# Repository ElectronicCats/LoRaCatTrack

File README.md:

# LoRaCat: Track

Electronic Cats invests time and resources providing this open source design, please support Electronic Cats and open-source hardware by purchasing products from Electronic Cats!

Designed by Electronic Cats.

Firmware released under an GNU AGPL v3.0 license. See the LICENSE file for more information.

Hardware released under an CERN Open Hardware Licence v1.2. See the LICENSE_HARDWARE file for more information.

Electronic Cats is a registered trademark, please do not use if you sell these PCBs.

23 Nov 2016

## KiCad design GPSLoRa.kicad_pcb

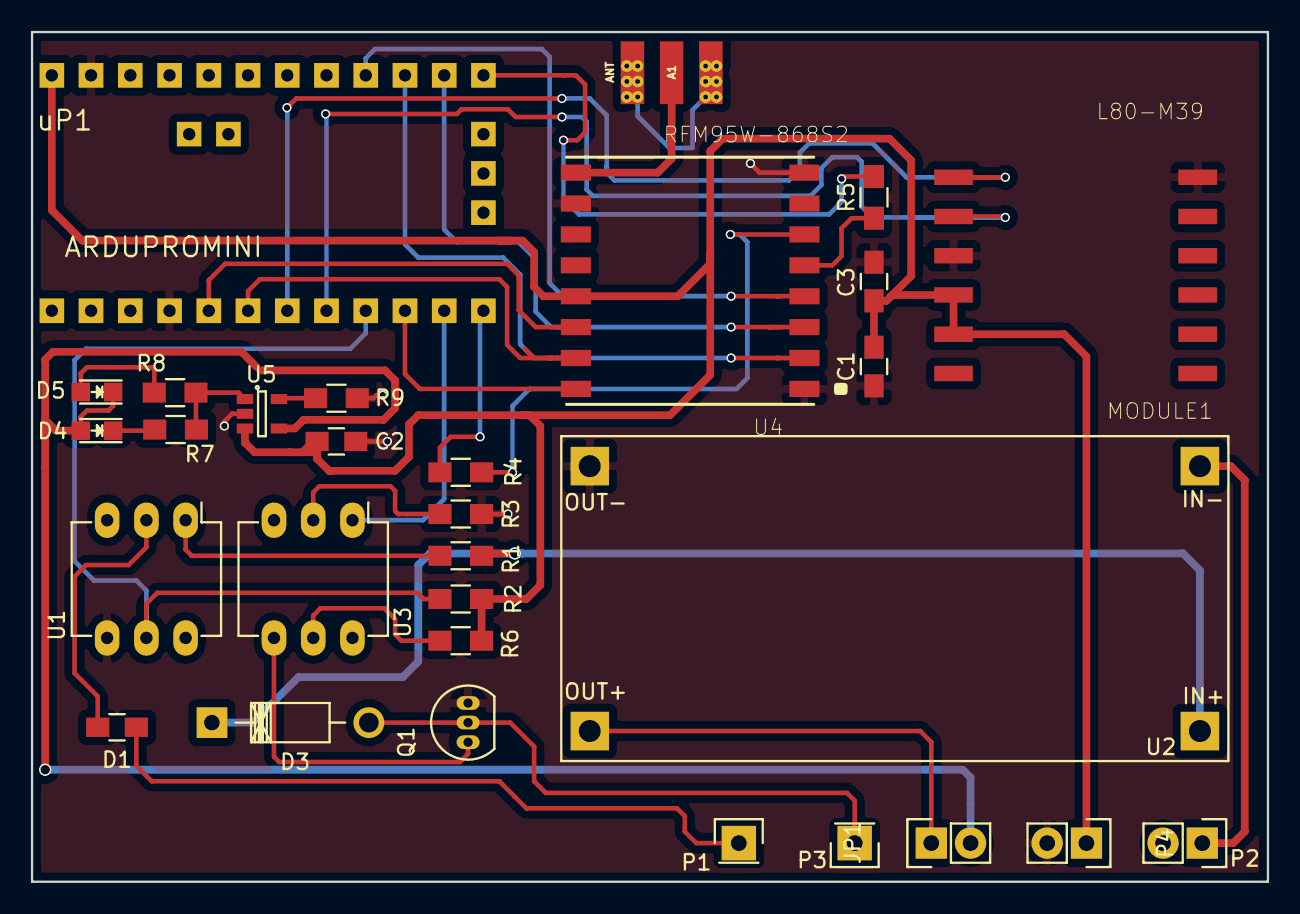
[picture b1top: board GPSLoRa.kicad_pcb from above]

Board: 2 copper layers, 80.0 x 55.0 mm, 30 parts (0 on the bottom side), 32 nets.

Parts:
A1: ANT; GSG-SMA-EDGE
C1, C3: 0.1uF; C_0805_HandSoldering
C2: 10uF; C_0805_HandSoldering
D1: D; C_0805_HandSoldering
D3: D; Diode_DO-41_SOD81_Horizontal_RM10
D4, D5: LED; LED_0805
JP1: JUMPER; Pin_Header_Straight_1x02
MODULE1: L80-M39; QUECTEL_L80-M39
P1: IN EXT; Pin_Header_Straight_1x01
P2: - INPUT 12 +; Pin_Header_Straight_1x02
P3: OUT EXT; Pin_Header_Straight_1x01
P4: Battery; Pin_Header_Straight_1x02
Q1: Q_NPN_BCE; TO-92_Inline_Narrow_Oval
R1, R6, R9: 1K; R_0805_HandSoldering
R2, R4, R5: 10K; R_0805_HandSoldering
R3, R7, R8: 220R; R_0805_HandSoldering
U1, U3: 4N26; DIP-6_W7.62mm_LongPads
U2: LM2596_Breakout; LM2596DC-DC
U4: RFM95W-868S2; XCVR_RFM95W-868S2
U5: MCP73831T-2ATI/OT; SOT-23-5
uP1: ARDUPROMINI; arduinoMiniPro2

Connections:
+5V: D4.2, D5.1, JP1.2, U5.4
+12C: D3.1, R1.1, U2.1
+BATT: C1.1, C2.1, C3.1, MODULE1.4, MODULE1.5, P4.1, R2.1, R6.1, U4.13, U5.3, uP1.19
/D6: R2.2, U1.5, uP1.15
/D8: U3.1, uP1.17
/DIO0: U4.14, uP1.11
/DIO1: U4.15, uP1.12
/DIO2: U4.16, uP1.16
/MISO: U4.2, uP1.28
/MOSI: U4.3, uP1.29
/NSS: R5.1, uP1.30
/RST: R4.1, uP1.18
/RX: MODULE1.2, uP1.14
/SCK: U4.4, uP1.27
/TX: MODULE1.1, uP1.13
GND: A1.2, A1.3, A1.4, A1.5, C1.2, C2.2, C3.2, MODULE1.3, MODULE1.12, P4.2, Q1.3, R3.2, R9.2, U1.4, U2.4, U4.1, U4.8, U4.10, U5.2, uP1.10, uP1.20
unnamed: A1.1, U4.9
unnamed: D1.1, P1.1
unnamed: D1.2, U1.2
unnamed: D3.2, P3.1, Q1.2
unnamed: D4.1, R7.2
unnamed: D5.2, R8.2
unnamed: JP1.1, U2.3
unnamed: P2.1, U2.2
unnamed: Q1.1, U3.4
unnamed: R1.2, U1.1
unnamed: R3.1, U3.2
unnamed: R4.2, U4.6
unnamed: R5.2, U4.5
unnamed: R6.2, U3.5
unnamed: R7.1, R8.1, U5.1
unnamed: R9.1, U5.5

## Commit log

2016-11-21 Added Squematic
2016-11-23 Working LoRa OTAA
2016-11-24 ChangeName LoRaCatTrack
2016-11-24 Added PDF v0.2
2016-11-25 Added PCB
2016-11-30 Modificado pines NSS y RST
2016-12-01 Working with GPS
2016-12-03 Update v0.3_beta
    Added button, added in external
2016-12-05 Added regulator 3.3v
2016-12-05 Update gitignore firmware
2016-12-14 Correct Pullup
2017-01-06 Added PCB 0.1v
2017-01-06 Add gitignore
2017-01-06 Added logos
2017-01-06 Check logos :3
